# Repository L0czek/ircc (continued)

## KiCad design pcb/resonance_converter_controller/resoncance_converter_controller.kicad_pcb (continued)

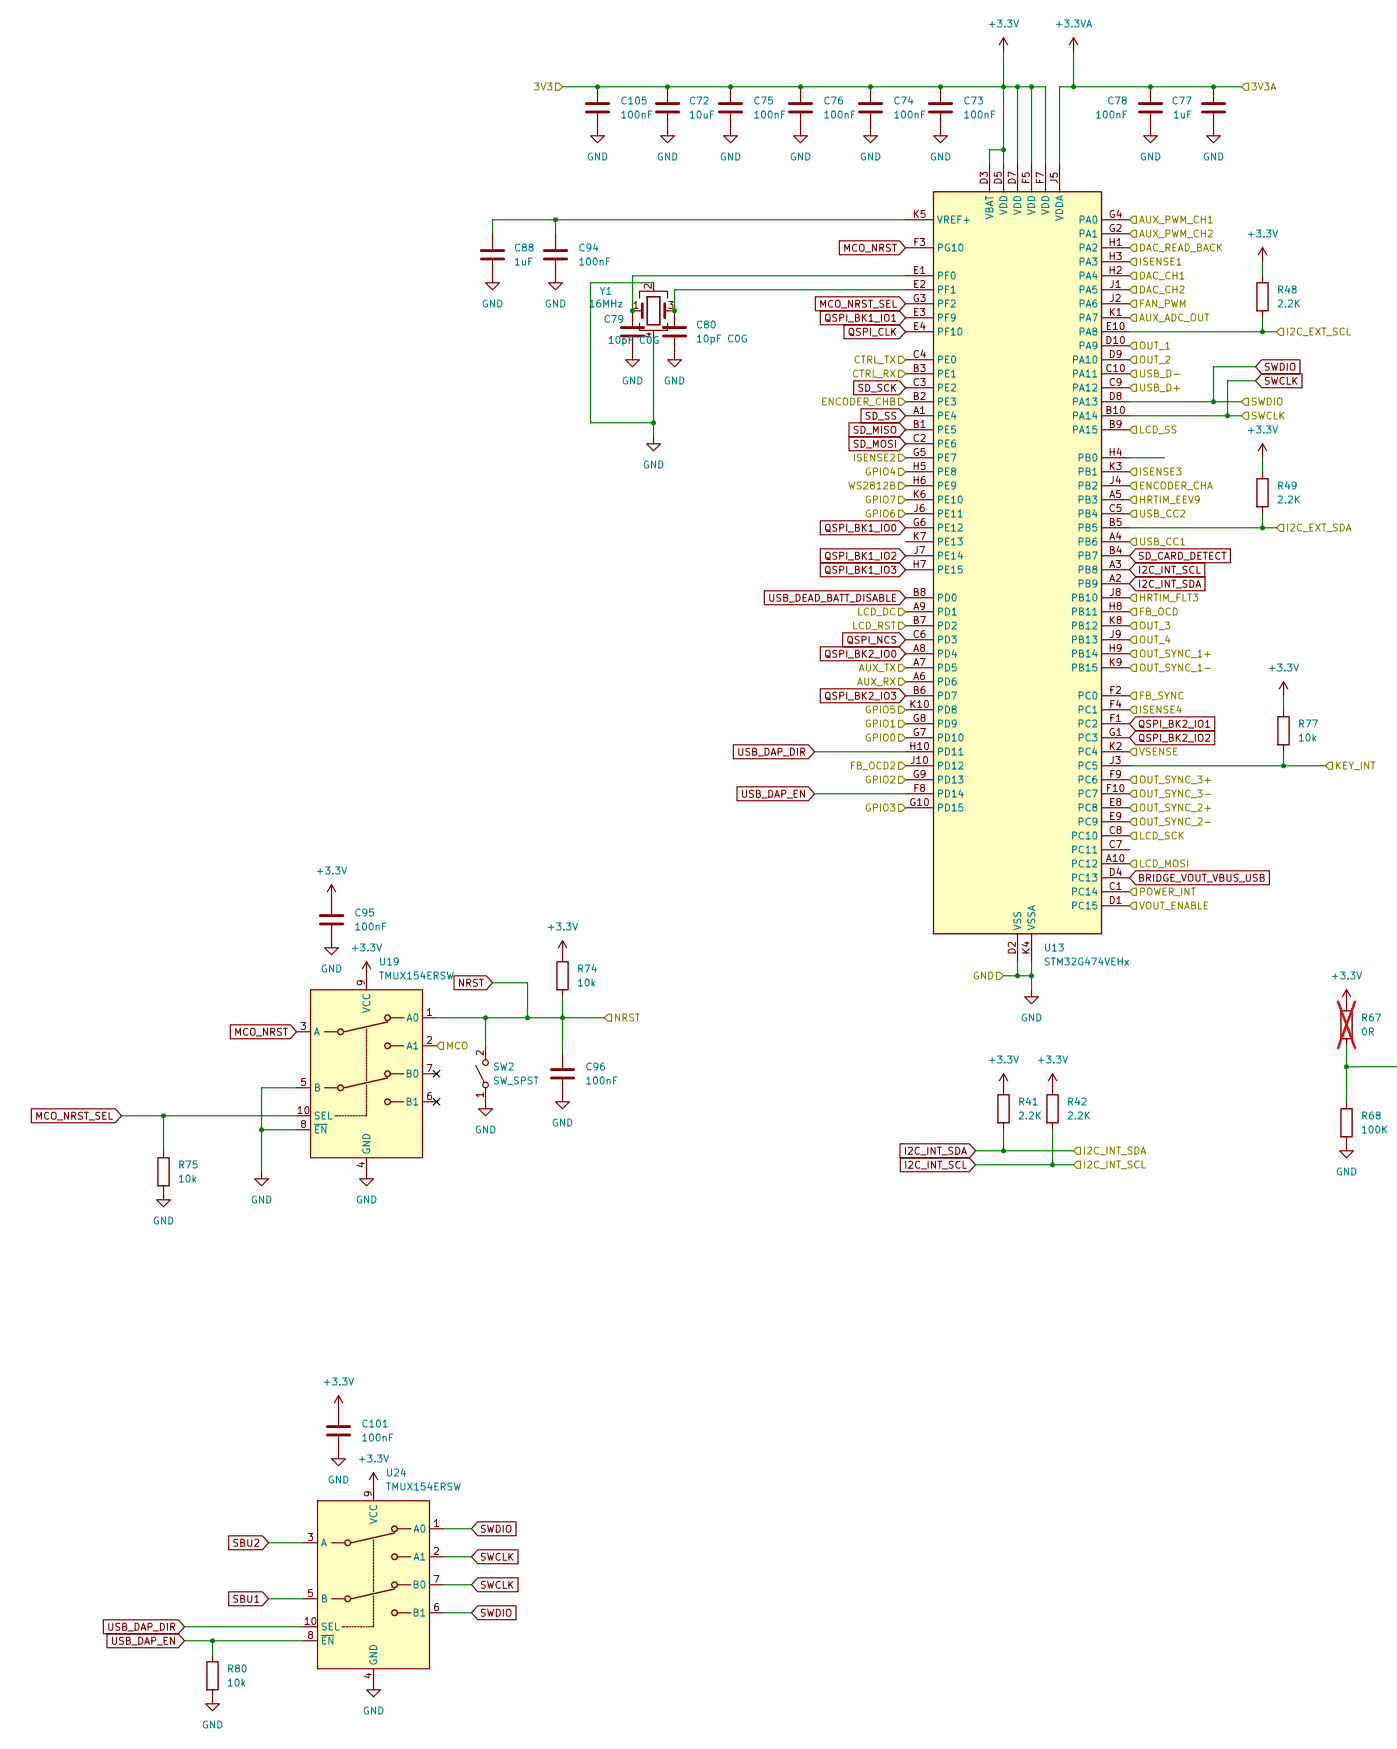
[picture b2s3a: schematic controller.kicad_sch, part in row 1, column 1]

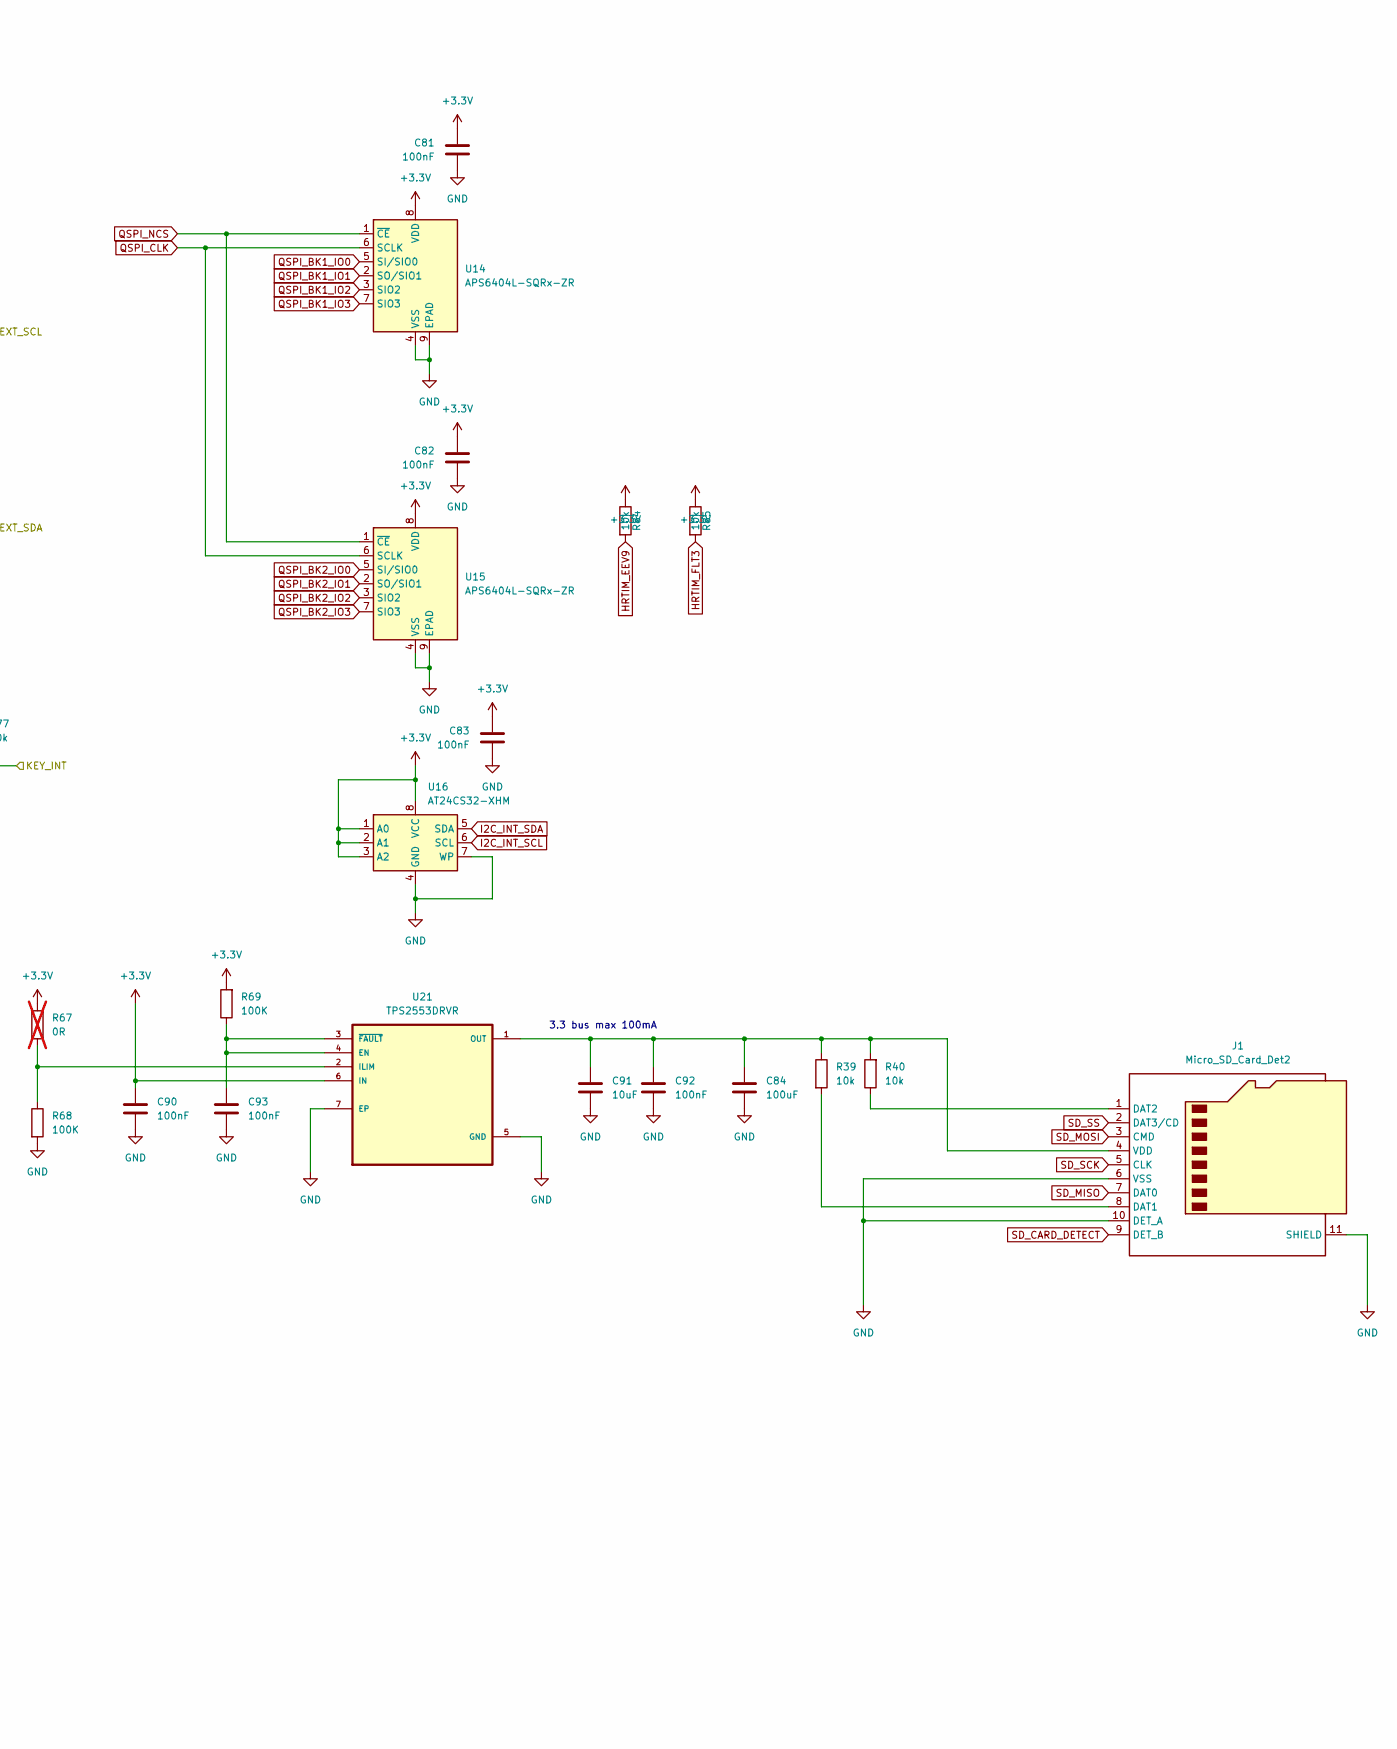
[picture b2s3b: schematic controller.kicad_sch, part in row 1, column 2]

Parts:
C72: 10uF; C_0805_2012Metric; LCSC C15850
C73, C74, C75, C76, C78, C81, C82, C83, C90, C92, C93, C94, C95, C96, C101, C105: 100nF; C_0402_1005Metric; LCSC C307331
C77: 1uF; C_0603_1608Metric; LCSC C15849
C79, C80: 10pF C0G; C_0402_1005Metric; MPN CL05C100JB5NNNC; LCSC C32949
C84: 100uF; C_1206_3216Metric; LCSC C15008
C88: 1uF; C_0402_1005Metric; LCSC C52923
C91: 10uF; C_1206_3216Metric; LCSC C13585
J1: Micro_SD_Card_Det2; microSD_HC_Hirose_DM3BT-DSF-PEJS
R39, R40, R74, R75, R77, R80, R84, R85: 10k; R_0402_1005Metric; LCSC C25744
R41, R42, R48, R49: 2.2K; R_0402_1005Metric; LCSC C25879
R67: 0R; R_0402_1005Metric; LCSC C17168; not fitted
R68, R69: 100K; R_0402_1005Metric; LCSC C25741
SW2: SW_SPST; SW_SPST_EVQPE1
U13: STM32G474VEHx; TFBGA-100_8x8mm_Layout10x10_P0.8mm
U14, U15: APS6404L-SQRx-ZR; Winbond_USON-8-1EP_3x2mm_P0.5mm_EP0.2x1.6mm
U16: AT24CS32-XHM; TSSOP-8_4.4x3mm_P0.65mm
U19, U24: TMUX154ERSW; UQFN-10_1.4x1.8mm_P0.4mm
U21: TPS2553DRVR; SON65P200X200X80-7N
Y1: 16MHz; Crystal_SMD_3225-4Pin_3.2x2.5mm; MPN X322516MLB4SI; LCSC C13738

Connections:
/Analog preprocess/DAC_IN: U13.H2 (PA4); also elsewhere on the board
/Analog preprocess/FB_OCD2_RECTIFIED: U13.J10 (PD12); also elsewhere on the board
/Analog preprocess/FB_OCD_RECTIFIED: U13.H8 (PB11); also elsewhere on the board
/Analog preprocess/FB_OUT: U13.F2 (PC0); also elsewhere on the board
/Analog preprocess/FB_SYNC_PADDING_V: U13.J1 (PA5); also elsewhere on the board
/Analog preprocess/ISENSE_1_OUT: U13.H3 (PA3); also elsewhere on the board
/Analog preprocess/ISENSE_2_OUT: U13.G5 (PE7); also elsewhere on the board
/Analog preprocess/ISENSE_3_OUT: U13.K3 (PB1); also elsewhere on the board
/Analog preprocess/ISENSE_4_OUT: U13.F4 (PC1); also elsewhere on the board
/Analog preprocess/VSENSE_OUT: U13.K2 (PC4); also elsewhere on the board
/Controller/AUX_PWM_CH1: U13.G4 (PA0); also elsewhere on the board
/Controller/AUX_PWM_CH2: U13.G2 (PA1); also elsewhere on the board
/Controller/OUT_1: U13.D10 (PA9); also elsewhere on the board
/Controller/OUT_2: U13.D9 (PA10); also elsewhere on the board
/Controller/OUT_3: U13.K8 (PB12); also elsewhere on the board
/Controller/OUT_4: U13.J9 (PB13); also elsewhere on the board
/Controller/OUT_SYNC_1+: U13.H9 (PB14); also elsewhere on the board
/Controller/OUT_SYNC_1-: U13.K9 (PB15); also elsewhere on the board
/Controller/OUT_SYNC_2+: U13.E8 (PC8); also elsewhere on the board
/Controller/OUT_SYNC_2-: U13.E9 (PC9); also elsewhere on the board
/Controller/OUT_SYNC_3+: U13.F9 (PC6); also elsewhere on the board
/Controller/OUT_SYNC_3-: U13.F10 (PC7); also elsewhere on the board
/Controller/VOUT_ENABLE: U13.D1 (PC15); also elsewhere on the board
/Controller/WS2812B: U13.H6 (PE9); also elsewhere on the board
AUX_ADC: U13.K1 (PA7); also elsewhere on the board
AUX_RX: U13.A6 (PD6); also elsewhere on the board
AUX_TX: U13.A7 (PD5); also elsewhere on the board
BRIDGE_VOUT_VBUS_USB: U13.D4 (PC13); also elsewhere on the board
CC1: U13.A4 (PB6); also elsewhere on the board
CC2: U13.C5 (PB4); also elsewhere on the board
CTRL_RX: U13.B3 (PE1); also elsewhere on the board
CTRL_TX: U13.C4 (PE0); also elsewhere on the board
DAC_OUT: U13.H1 (PA2); also elsewhere on the board
ENCODER_CHA: U13.J4 (PB2); also elsewhere on the board
ENCODER_CHB: U13.B2 (PE3); also elsewhere on the board
FAN_PWM: U13.J2 (PA6); also elsewhere on the board
GND: C72.2, C73.2, C74.2, C75.2, C76.2, C77.2, C78.2, C79.2, C80.2, C81.2, C82.2, C83.2, C84.2, C88.2, C90.2, C91.2, C92.2, C93.2, C94.2, C95.2, C96.2, C101.2, C105.2, J1.6 (VSS), J1.10 (DET_A), J1.11 (SHIELD), R68.2, R75.2, R80.2, SW2.1 (A), U13.D2 (VSS), U13.D6 (VSS), U13.E5 (VSS), U13.E6 (VSS), U13.E7 (VSS), U13.F6 (VSS), U13.K4 (VSSA), U14.4 (VSS), U14.9 (EPAD), U15.4 (VSS), U15.9 (EPAD), U16.4 (GND), U16.7 (WP), U19.4 (GND), U19.5 (B), U19.8 (~EN), U21.5 (GND), U21.7 (EP), U24.4 (GND), Y1.2, Y1.4; also elsewhere on the board
GPIO0: U13.G7 (PD10); also elsewhere on the board
GPIO1: U13.G8 (PD9); also elsewhere on the board
GPIO2: U13.G9 (PD13); also elsewhere on the board
GPIO3: U13.G10 (PD15); also elsewhere on the board
GPIO4: U13.H5 (PE8); also elsewhere on the board
GPIO5: U13.K10 (PD8); also elsewhere on the board
GPIO6: U13.J6 (PE11); also elsewhere on the board
GPIO7: U13.K6 (PE10); also elsewhere on the board
HRTIM_EEV9: R84.2, U13.A5 (PB3); also elsewhere on the board
HRTIM_FLT3: R85.2, U13.J8 (PB10); also elsewhere on the board
I2C_EXT_SCL: R48.2, U13.E10 (PA8); also elsewhere on the board
I2C_EXT_SDA: R49.2, U13.B5; also elsewhere on the board
INT_I2C_SCL: R42.2, U13.A3 (PB8), U16.6 (SCL); also elsewhere on the board
INT_I2C_SDA: R41.2, U13.A2 (PB9), U16.5 (SDA); also elsewhere on the board
KEY_INT: R77.2, U13.J3 (PC5); also elsewhere on the board
LCD_DC: U13.A9 (PD1); also elsewhere on the board
LCD_MOSI: U13.A10 (PC12); also elsewhere on the board
LCD_RST: U13.B7 (PD2); also elsewhere on the board
LCD_SCK: U13.C8 (PC10); also elsewhere on the board
LCD_SS: U13.B9 (PA15); also elsewhere on the board
MCO: U19.2 (A1); also elsewhere on the board
MCO_NRST: U13.F3 (PG10), U19.3 (A)
MCO_NRST_SEL: R75.1, U13.G3 (PF2), U19.10 (SEL)
NRST: C96.1, R74.2, SW2.2 (B), U19.1 (A0); also elsewhere on the board
unnamed: J1.8 (DAT1), R39.2
unnamed: J1.1 (DAT2), R40.1
unnamed: C84.1, C91.1, C92.1, J1.4 (VDD), R39.1, R40.2, U21.1 (OUT)
unnamed: C79.1, U13.E1 (PF0), Y1.1
unnamed: C80.1, U13.E2 (PF1), Y1.3
unnamed: C88.1, C94.1, U13.K5 (VREF+)
unnamed: C93.1, R69.1, U21.3 (~FAULT), U21.4 (EN)
unnamed: R67.2, R68.1, U21.2 (ILIM)
QSPI_BK1_IO0: U13.G6 (PE12), U14.5 (SI/SIO0)
QSPI_BK1_IO1: U13.E3 (PF9), U14.2 (SO/SIO1)
QSPI_BK1_IO2: U13.J7 (PE14), U14.3 (SIO2)
QSPI_BK1_IO3: U13.H7 (PE15), U14.7 (SIO3)
QSPI_BK2_IO0: U13.A8 (PD4), U15.5 (SI/SIO0)
QSPI_BK2_IO1: U13.F1 (PC2), U15.2 (SO/SIO1)
QSPI_BK2_IO2: U13.G1 (PC3), U15.3 (SIO2)
QSPI_BK2_IO3: U13.B6 (PD7), U15.7 (SIO3)
QSPI_CLK: U13.E4 (PF10), U14.6 (SCLK), U15.6 (SCLK)
QSPI_NCS: U13.C6 (PD3), U14.1 (~CE), U15.1 (~CE)
SBU1: U24.5 (B); also elsewhere on the board
SBU2: U24.3 (A); also elsewhere on the board
SD_CARD_DETECT: J1.9 (DET_B), U13.B4 (PB7)
SD_MISO: J1.7 (DAT0), U13.B1 (PE5)
SD_MOSI: J1.3 (CMD), U13.C2 (PE6)
SD_SCK: J1.5 (CLK), U13.C3 (PE2)
SD_SS: J1.2 (DAT3/CD), U13.A1 (PE4)
SWCLK: U13.B10 (PA14), U24.2 (A1), U24.7 (B0); also elsewhere on the board
SWDIO: U13.D8 (PA13), U24.1 (A0), U24.6 (B1); also elsewhere on the board
USB_D+: U13.C9 (PA12); also elsewhere on the board
USB_D-: U13.C10 (PA11); also elsewhere on the board
USB_DAP_DIR: U13.H10 (PD11), U24.10 (SEL)
USB_DAP_EN: R80.1, U13.F8 (PD14), U24.8 (~EN)
USB_DEAD_BATT_DISABLE: U13.B8 (PD0); also elsewhere on the board
VAA: C77.1, C78.1, U13.J5 (VDDA); also elsewhere on the board
VCC: C72.1, C73.1, C74.1, C75.1, C76.1, C81.1, C82.1, C83.1, C90.1, C95.1, C101.1, C105.1, R41.1, R42.1, R48.1, R49.1, R67.1, R69.2, R74.1, R77.1, R84.1, R85.1, U13.D3 (VBAT), U13.D5 (VDD), U13.D7 (VDD), U13.F5 (VDD), U13.F7 (VDD), U14.8 (VDD), U15.8 (VDD), U16.1 (A0), U16.2 (A1), U16.3 (A2), U16.8 (VCC), U19.9 (VCC), U21.6 (IN), U24.9 (VCC); also elsewhere on the board
/INT: U13.C1 (PC14); also elsewhere on the board

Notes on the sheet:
3.3 bus max 100mA

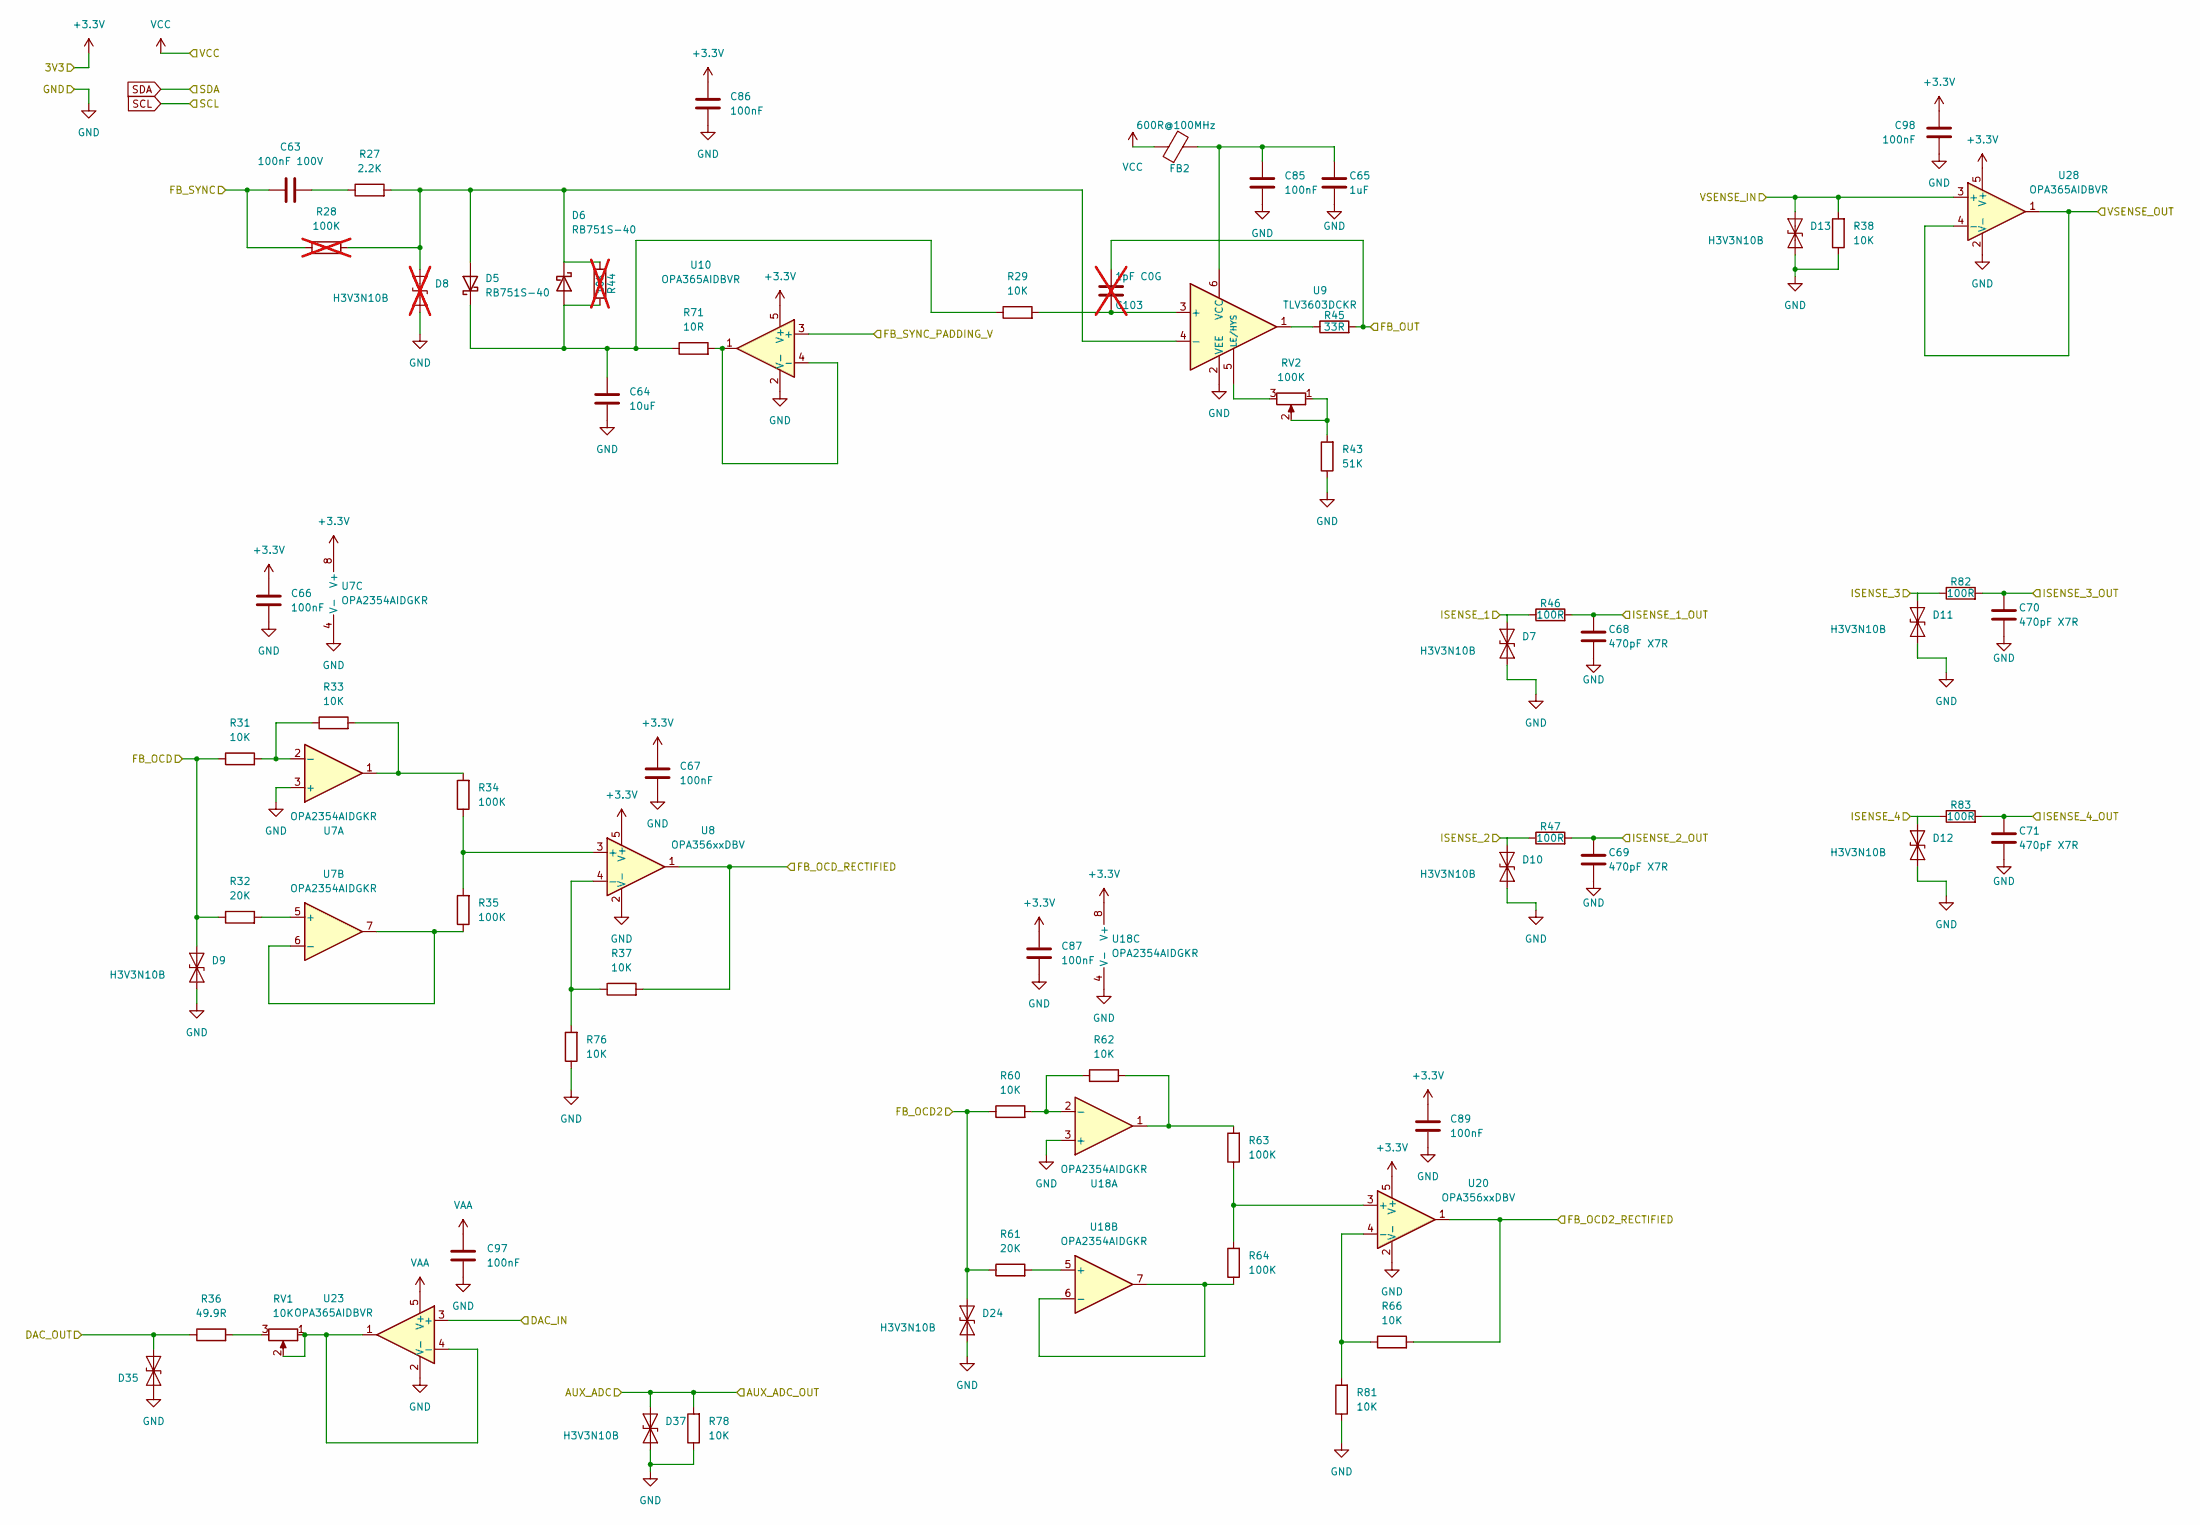
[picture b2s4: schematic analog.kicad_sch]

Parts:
C63: 100nF 100V; C_1206_3216Metric; LCSC C110255
C64: 10uF; C_1206_3216Metric; LCSC C13585
C65: 1uF; C_0402_1005Metric; LCSC C52923
C66, C67, C85, C86, C87, C89, C97, C98: 100nF; C_0402_1005Metric; LCSC C307331
C68, C69, C70, C71: 470pF X7R; C_0402_1005Metric; LCSC C1537
C103: 1pF C0G; C_0402_1005Metric; LCSC C1550; not fitted
D5, D6: RB751S-40; D_SOD-523; MPN RB751S-40; LCSC C7502700
D7, D9, D10, D11, D12, D13, D24, D35, D37: H3V3N10B; D_0402_1005Metric; LCSC C20617909
D8: H3V3N10B; D_0402_1005Metric; LCSC C20617909; not fitted
FB2: 600R@100MHz; L_0603_1608Metric; MPN GZ1608D601TF; LCSC C1002
R27: 2.2K; R_2512_6332Metric; LCSC C421608
R28: 100K; R_1206_3216Metric; LCSC C17900; not fitted
R29, R31, R33, R37, R38, R60, R62, R66, R76, R78, R81: 10K; R_0402_1005Metric; LCSC C25744
R32, R61: 20K; R_0402_1005Metric; LCSC C25765
R34, R35, R63, R64: 100K; R_0402_1005Metric; LCSC C25741
R36: 49.9R; R_0402_1005Metric; LCSC C25120
R43: 51K; R_0402_1005Metric; LCSC C25794
R44: 10K; R_0402_1005Metric; LCSC C25744; not fitted
R45: 33R; R_0402_1005Metric; LCSC C25105
R46, R47, R82, R83: 100R; R_0402_1005Metric; LCSC C25076
R71: 10R; R_0402_1005Metric; LCSC C25077
RV1: 10K; Potentiometer_Bourns_3224J_Horizontal
RV2: 100K; Potentiometer_Bourns_3224J_Horizontal
U7, U18: OPA2354AIDGKR; VSSOP-8_3x3mm_P0.65mm; LCSC C95502
U8, U20: OPA356xxDBV; SOT-23-5
U9: TLV3603DCKR; SOT-363_SC-70-6; LCSC C5213955
U10, U23, U28: OPA365AIDBVR; SOT-23-5; LCSC C96626

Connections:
/Analog preprocess/DAC_IN: U23.3 (+); also elsewhere on the board
/Analog preprocess/FB_OCD2_RECTIFIED: R66.2, U20.1; also elsewhere on the board
/Analog preprocess/FB_OCD_RECTIFIED: R37.2, U8.1; also elsewhere on the board
/Analog preprocess/FB_OUT: C103.1, R45.2; also elsewhere on the board
/Analog preprocess/FB_SYNC_PADDING_V: U10.3 (+); also elsewhere on the board
/Analog preprocess/ISENSE_1_OUT: C68.1, R46.2; also elsewhere on the board
/Analog preprocess/ISENSE_2_OUT: C69.1, R47.2; also elsewhere on the board
/Analog preprocess/ISENSE_3_OUT: C70.1, R82.2; also elsewhere on the board
/Analog preprocess/ISENSE_4_OUT: C71.1, R83.2; also elsewhere on the board
/Analog preprocess/VSENSE_OUT: U28.1, U28.4 (-); also elsewhere on the board
AUX_ADC: D37.2 (A2), R78.2; also elsewhere on the board
DAC_OUT: D35.1 (A1), R36.1; also elsewhere on the board
FB_IN: C63.1, R28.1; also elsewhere on the board
GND: C64.1, C65.2, C66.1, C67.1, C68.2, C69.2, C70.2, C71.2, C85.1, C86.1, C87.1, C89.1, C97.2, C98.2, D7.1 (A1), D8.1 (A1), D9.1 (A1), D10.1 (A1), D11.1 (A1), D12.1 (A1), D13.1 (A1), D24.1 (A1), D35.2 (A2), D37.1 (A1), R38.1, R43.1, R76.1, R78.1, R81.1, U7.3 (+), U7.4 (V-), U8.2 (V-), U9.2 (VEE), U10.2 (V-), U18.3 (+), U18.4 (V-), U20.2 (V-), U23.2 (V-), U28.2 (V-); also elsewhere on the board
ISENSE_1: D7.2 (A2), R46.1; also elsewhere on the board
ISENSE_2: D10.2 (A2), R47.1; also elsewhere on the board
ISENSE_3: D11.2 (A2), R82.1; also elsewhere on the board
ISENSE_4: D12.2 (A2), R83.1; also elsewhere on the board
unnamed: C63.2, R27.1
unnamed: D5.2 (A), D6.1 (K), D8.2 (A2), R27.2, R28.2, R44.1, U9.4 (-)
unnamed: C64.2, D5.1 (K), D6.2 (A), R29.1, R44.2, R71.1
unnamed: R33.2, R34.2, U7.1
unnamed: R36.2, RV1.3
unnamed: R43.2, RV2.1, RV2.2
unnamed: R45.1, U9.1
unnamed: R62.2, R63.2, U18.1
unnamed: R31.2, R33.1, U7.2 (-)
unnamed: R32.2, U7.5 (+)
unnamed: R35.1, U7.6 (-), U7.7
unnamed: R34.1, R35.2, U8.3 (+)
unnamed: R37.1, R76.2, U8.4 (-)
unnamed: C103.2, R29.2, U9.3 (+)
unnamed: RV2.3, U9.5 (LE/HYS)
unnamed: C65.1, C85.2, FB2.2, U9.6 (VCC)
unnamed: R71.2, U10.1, U10.4 (-)
unnamed: R60.2, R62.1, U18.2 (-)
unnamed: R61.2, U18.5 (+)
unnamed: R64.1, U18.6 (-), U18.7
unnamed: R63.1, R64.2, U20.3 (+)
unnamed: R66.1, R81.2, U20.4 (-)
unnamed: RV1.1, RV1.2, U23.1, U23.4 (-)
OCD2_IN: D24.2 (A2), R60.1, R61.1; also elsewhere on the board
OCD_IN: D9.2 (A2), R31.1, R32.1; also elsewhere on the board
VAA: C66.2, C67.2, C86.2, C87.2, C89.2, C97.1, C98.1, U7.8 (V+), U8.5 (V+), U10.5 (V+), U18.8 (V+), U20.5 (V+), U23.5 (V+), U28.5 (V+); also elsewhere on the board
VCC: FB2.1; also elsewhere on the board
VSENSE_IN: D13.2 (A2), R38.2, U28.3 (+); also elsewhere on the board
